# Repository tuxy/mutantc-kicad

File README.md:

# mutantC-kicad
(attempted) remake of the mutantC v4 on KiCAD

Right now:
- The main pcb is incomplete
- The thumbstick pcb is partially complete
	- All of the functionality is done, I just need to position everything correctly
- The display PCB is complete (Components are different and also positioned differently, but should still work flawlessly?)

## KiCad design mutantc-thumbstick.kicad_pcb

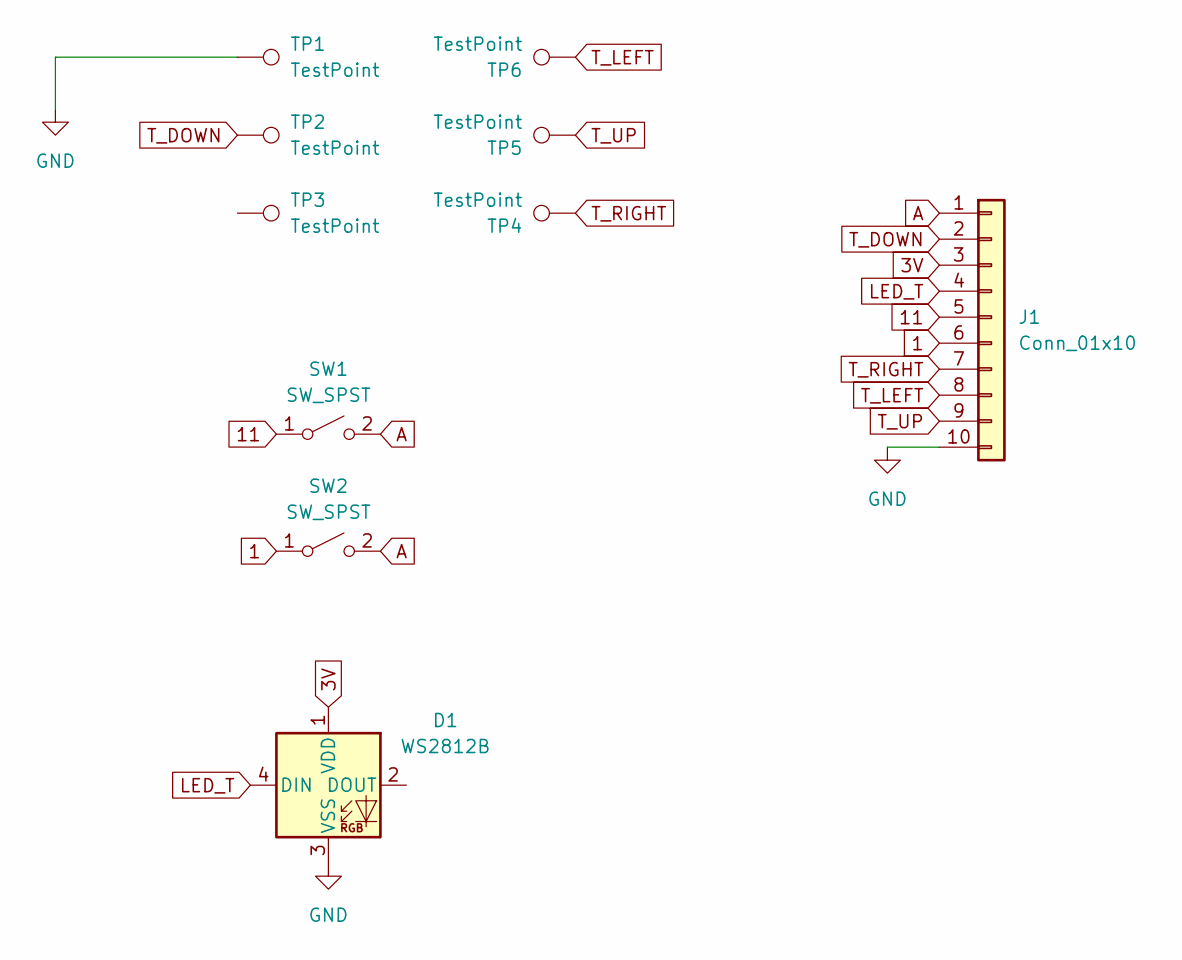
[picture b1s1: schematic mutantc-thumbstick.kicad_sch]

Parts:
D1: WS2812B; LED_WS2812B_PLCC4_5.0x5.0mm_P3.2mm
J1: Conn_01x10; TE_1-84952-0_1x10-1MP_P1.0mm_Horizontal
SW1, SW2: SW_SPST; SW_Push_1P1T_NO_CK_KMR2
TP1, TP2, TP3, TP4, TP5, TP6: TestPoint; TestPoint_Pad_1.0x1.0mm

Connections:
1: J1.6, SW2.1 (A)
3V: D1.1 (VDD), J1.3
11: J1.5, SW1.1 (A)
A: J1.1, SW1.2 (B), SW2.2 (B)
GND: D1.3 (VSS), J1.10, TP1.1
LED_T: D1.4 (DIN), J1.4
T_DOWN: J1.2, TP2.1
T_LEFT: J1.8, TP6.1
T_RIGHT: J1.7, TP4.1
T_UP: J1.9, TP5.1

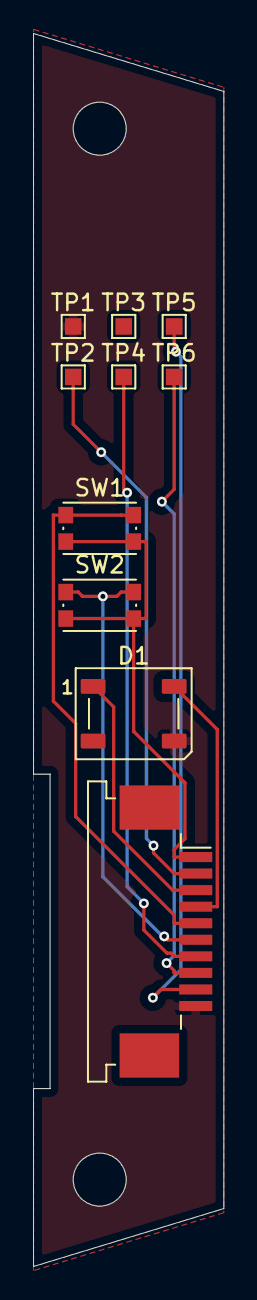
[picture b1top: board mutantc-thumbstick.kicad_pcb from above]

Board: 2 copper layers, 11.5 x 74.5 mm, 10 parts (0 on the bottom side), 10 nets.

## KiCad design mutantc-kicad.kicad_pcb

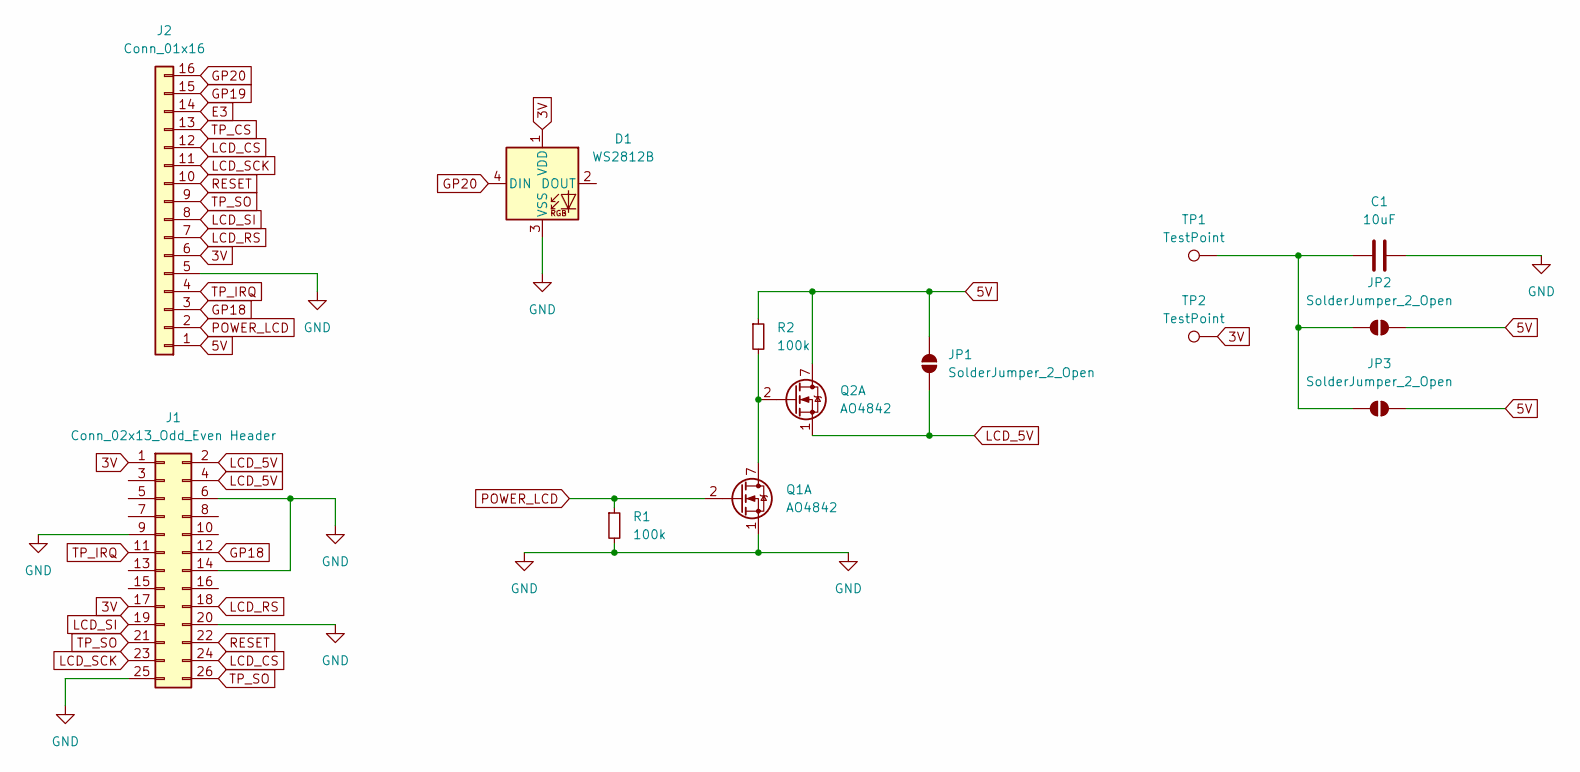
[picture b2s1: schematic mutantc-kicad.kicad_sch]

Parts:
C1: 10uF; C_1206_3216Metric
D1: WS2812B; LED_WS2812B_PLCC4_5.0x5.0mm_P3.2mm
J1: Conn_02x13_Odd_Even Header; PinHeader_2x13_P2.54mm_Vertical
J2: Conn_01x16; TE_1-84953-6_1x16-1MP_P1.0mm_Horizontal
JP1, JP2, JP3: SolderJumper_2_Open; SolderJumper-2_P1.3mm_Open_RoundedPad1.0x1.5mm
Q1, Q2: AO4842; SOIC-8_3.9x4.9mm_P1.27mm
R1, R2: 100k; R_1206_3216Metric
TP1, TP2: TestPoint; TestPoint_THTPad_D1.0mm_Drill0.5mm

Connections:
3V: D1.1 (VDD), J1.1, J1.17, J2.6, TP2.1
5V: J2.1, JP1.2 (B), JP2.1 (A), JP3.1 (A), Q2.7 (D1), Q2.8 (D1), R2.1
E3: J2.14
GND: C1.1, D1.3 (VSS), J1.6, J1.9, J1.14, J1.20, J1.25, J2.5, Q1.1 (S1), R1.2
GP18: J1.12, J2.3
GP19: J2.15
GP20: D1.4 (DIN), J2.16
LCD_5V: J1.2, J1.4, JP1.1 (A), Q2.1 (S1)
LCD_CS: J1.24, J2.12
LCD_RS: J1.18, J2.7
LCD_SCK: J1.23, J2.11
LCD_SI: J1.19, J2.8
unnamed: C1.2, JP2.2 (B), JP3.2 (B), TP1.1
unnamed: Q1.7 (D1), Q1.8 (D1), Q2.2 (G1), R2.2
POWER_LCD: J2.2, Q1.2 (G1), R1.1
RESET: J1.22, J2.10
TP_CS: J2.13
TP_IRQ: J1.11, J2.4
TP_SO: J1.21, J1.26, J2.9

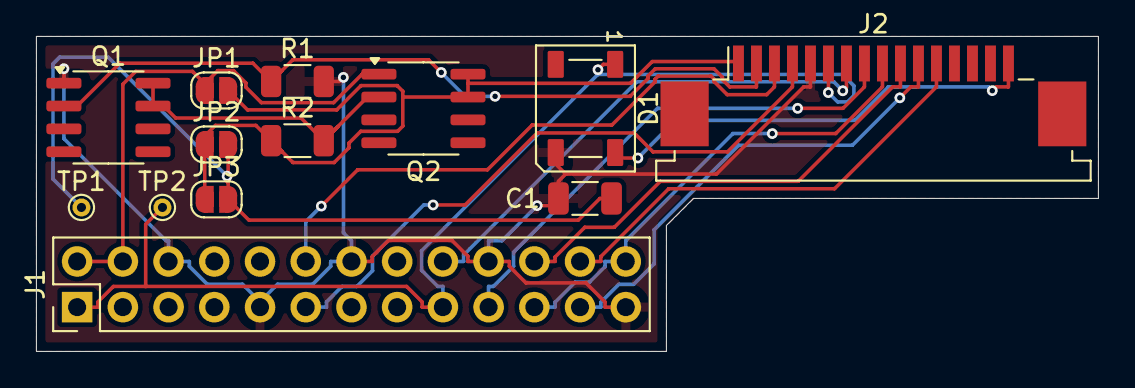
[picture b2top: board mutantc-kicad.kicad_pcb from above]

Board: 2 copper layers, 59.0 x 17.5 mm, 13 parts (0 on the bottom side), 16 nets.

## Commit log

2025-02-21 Added keyboard matrix to main
